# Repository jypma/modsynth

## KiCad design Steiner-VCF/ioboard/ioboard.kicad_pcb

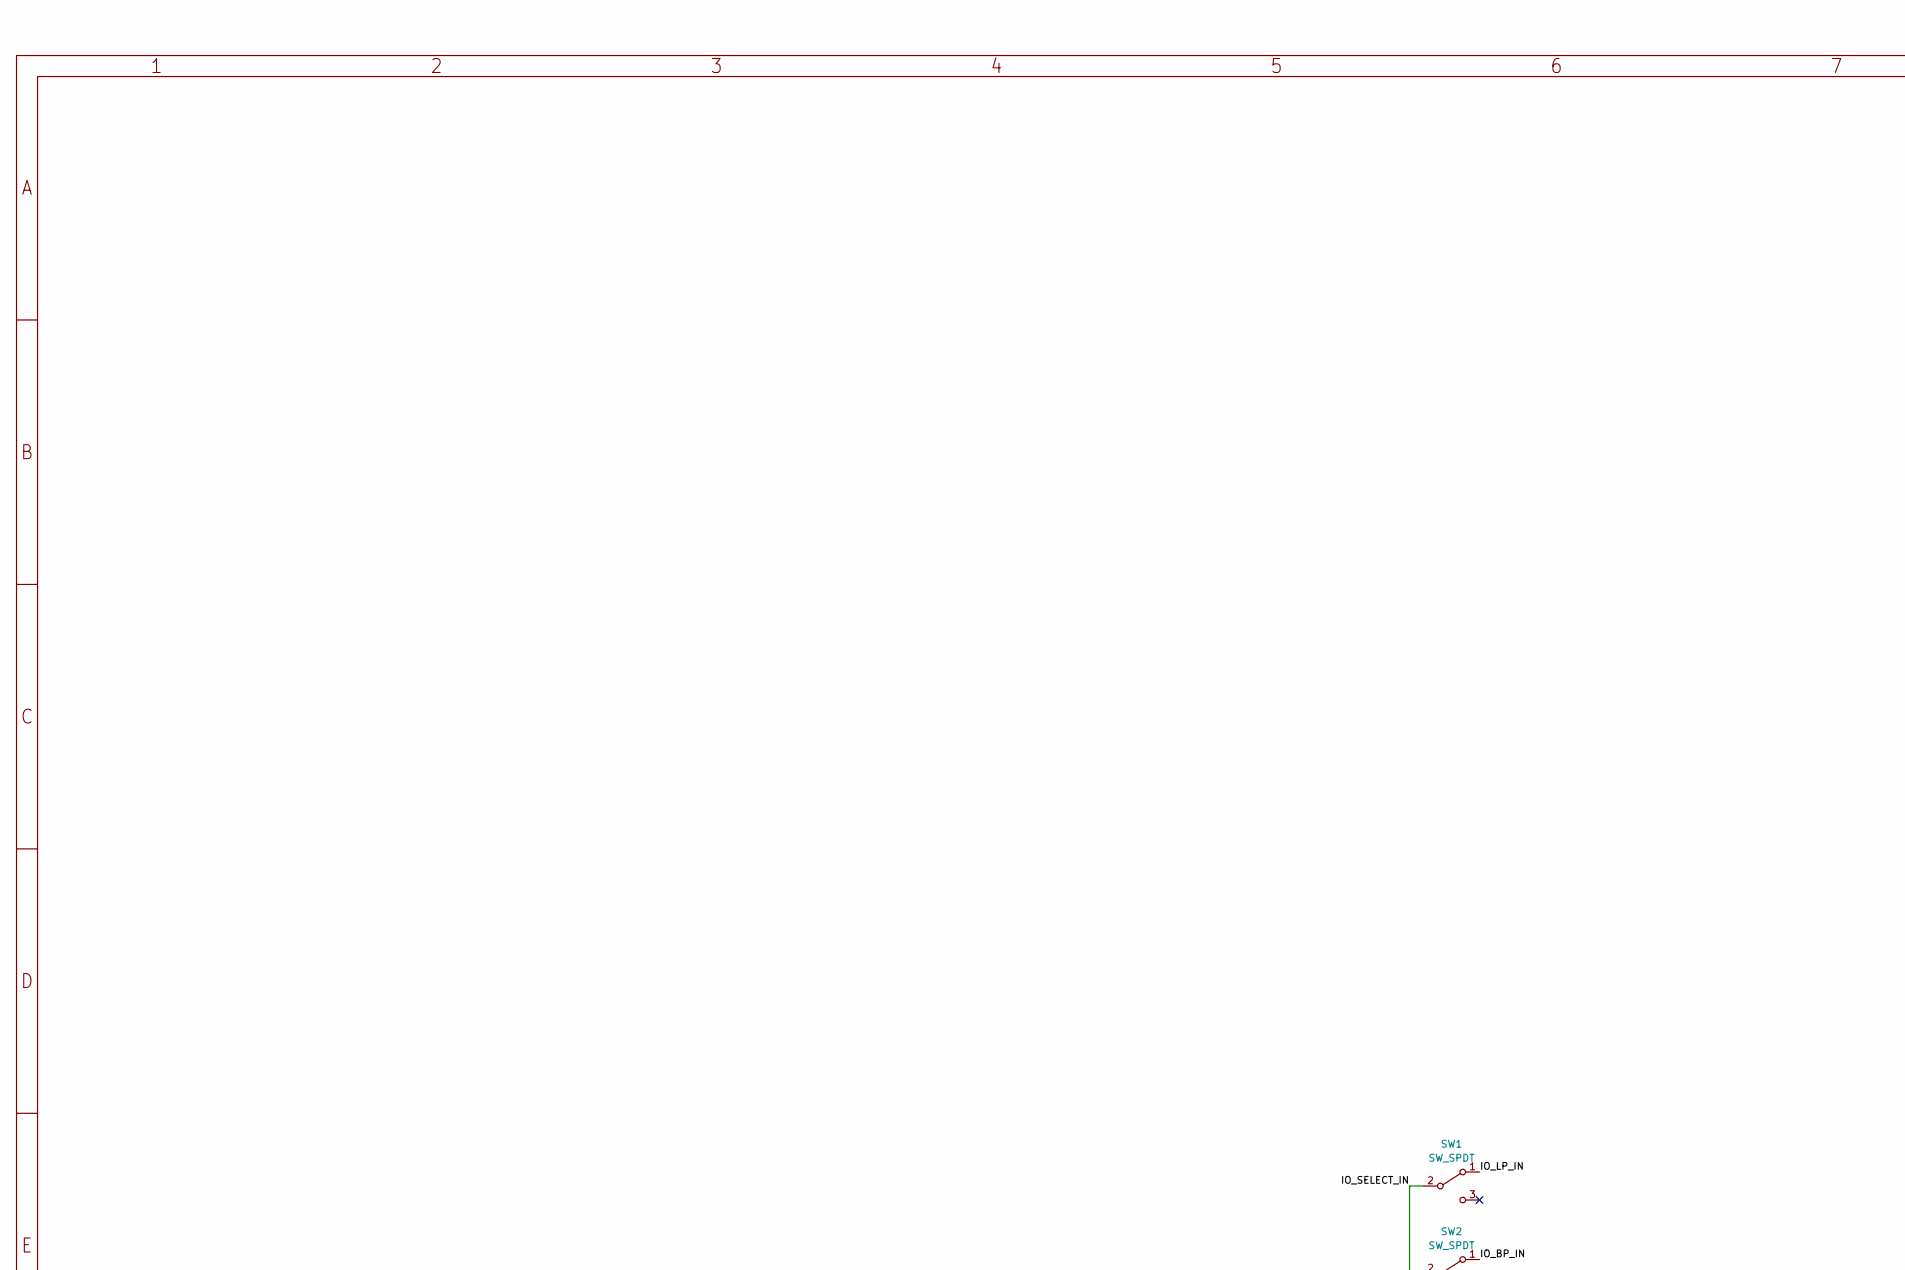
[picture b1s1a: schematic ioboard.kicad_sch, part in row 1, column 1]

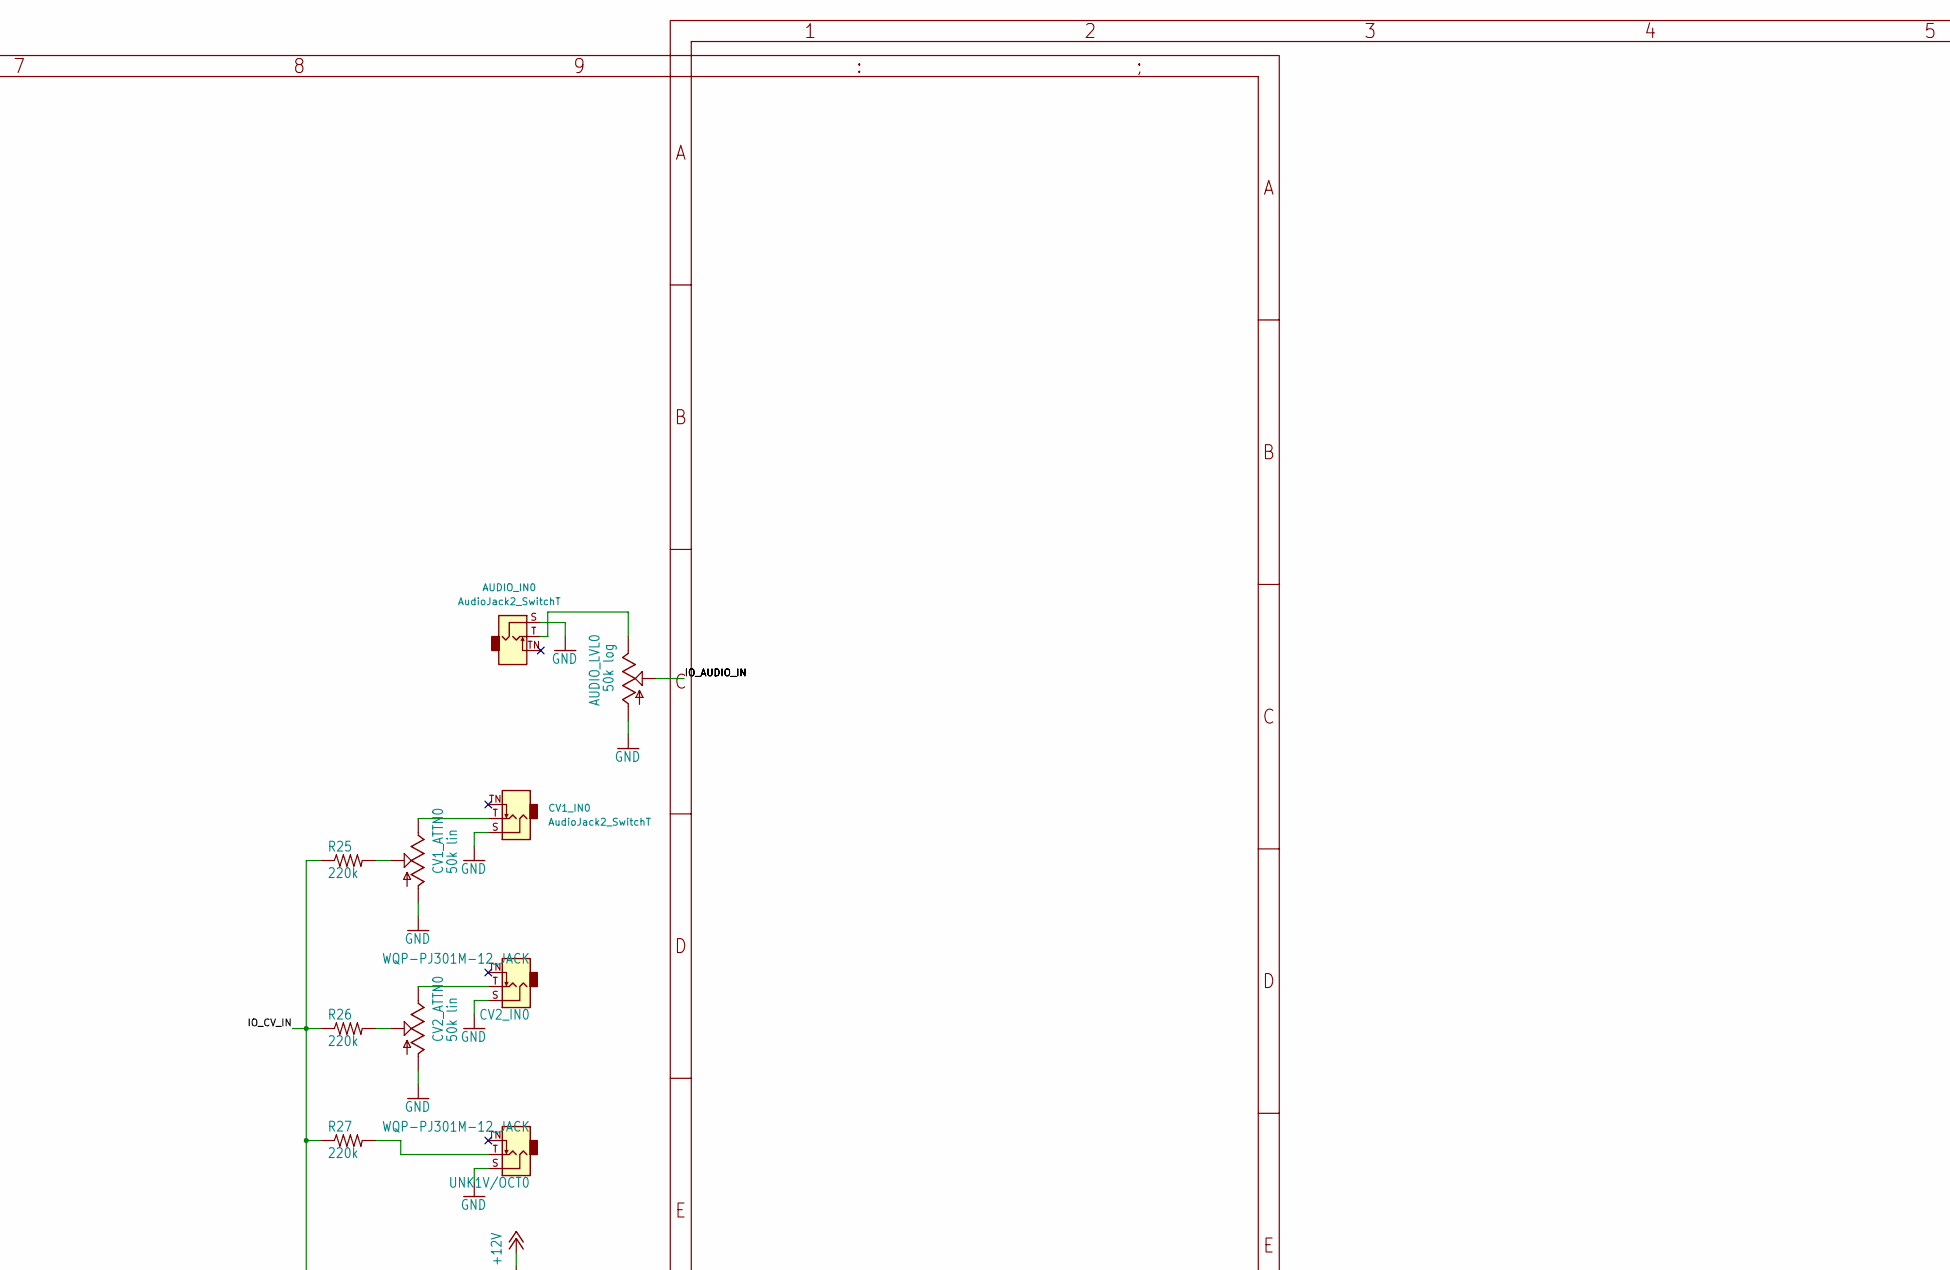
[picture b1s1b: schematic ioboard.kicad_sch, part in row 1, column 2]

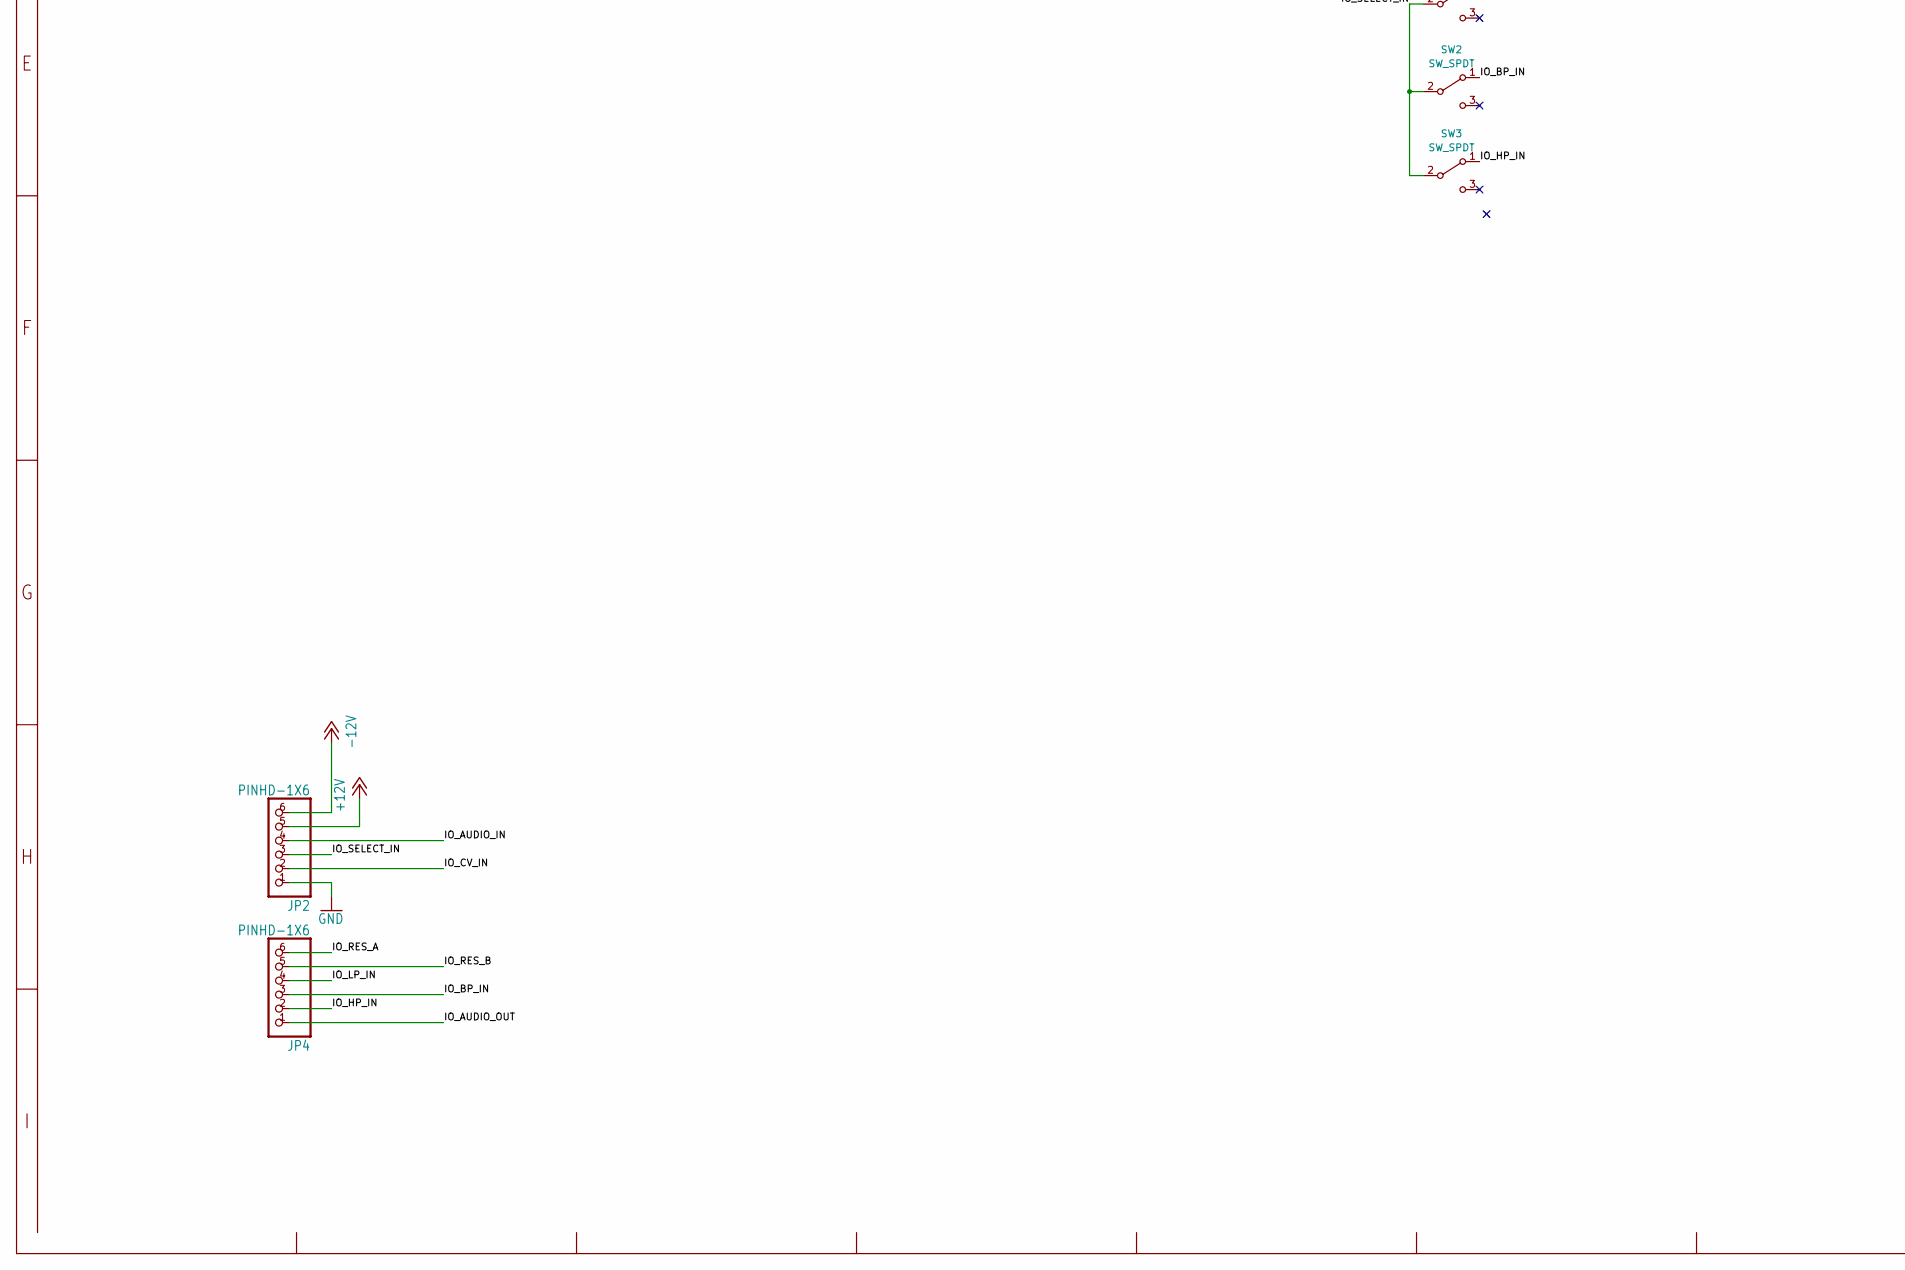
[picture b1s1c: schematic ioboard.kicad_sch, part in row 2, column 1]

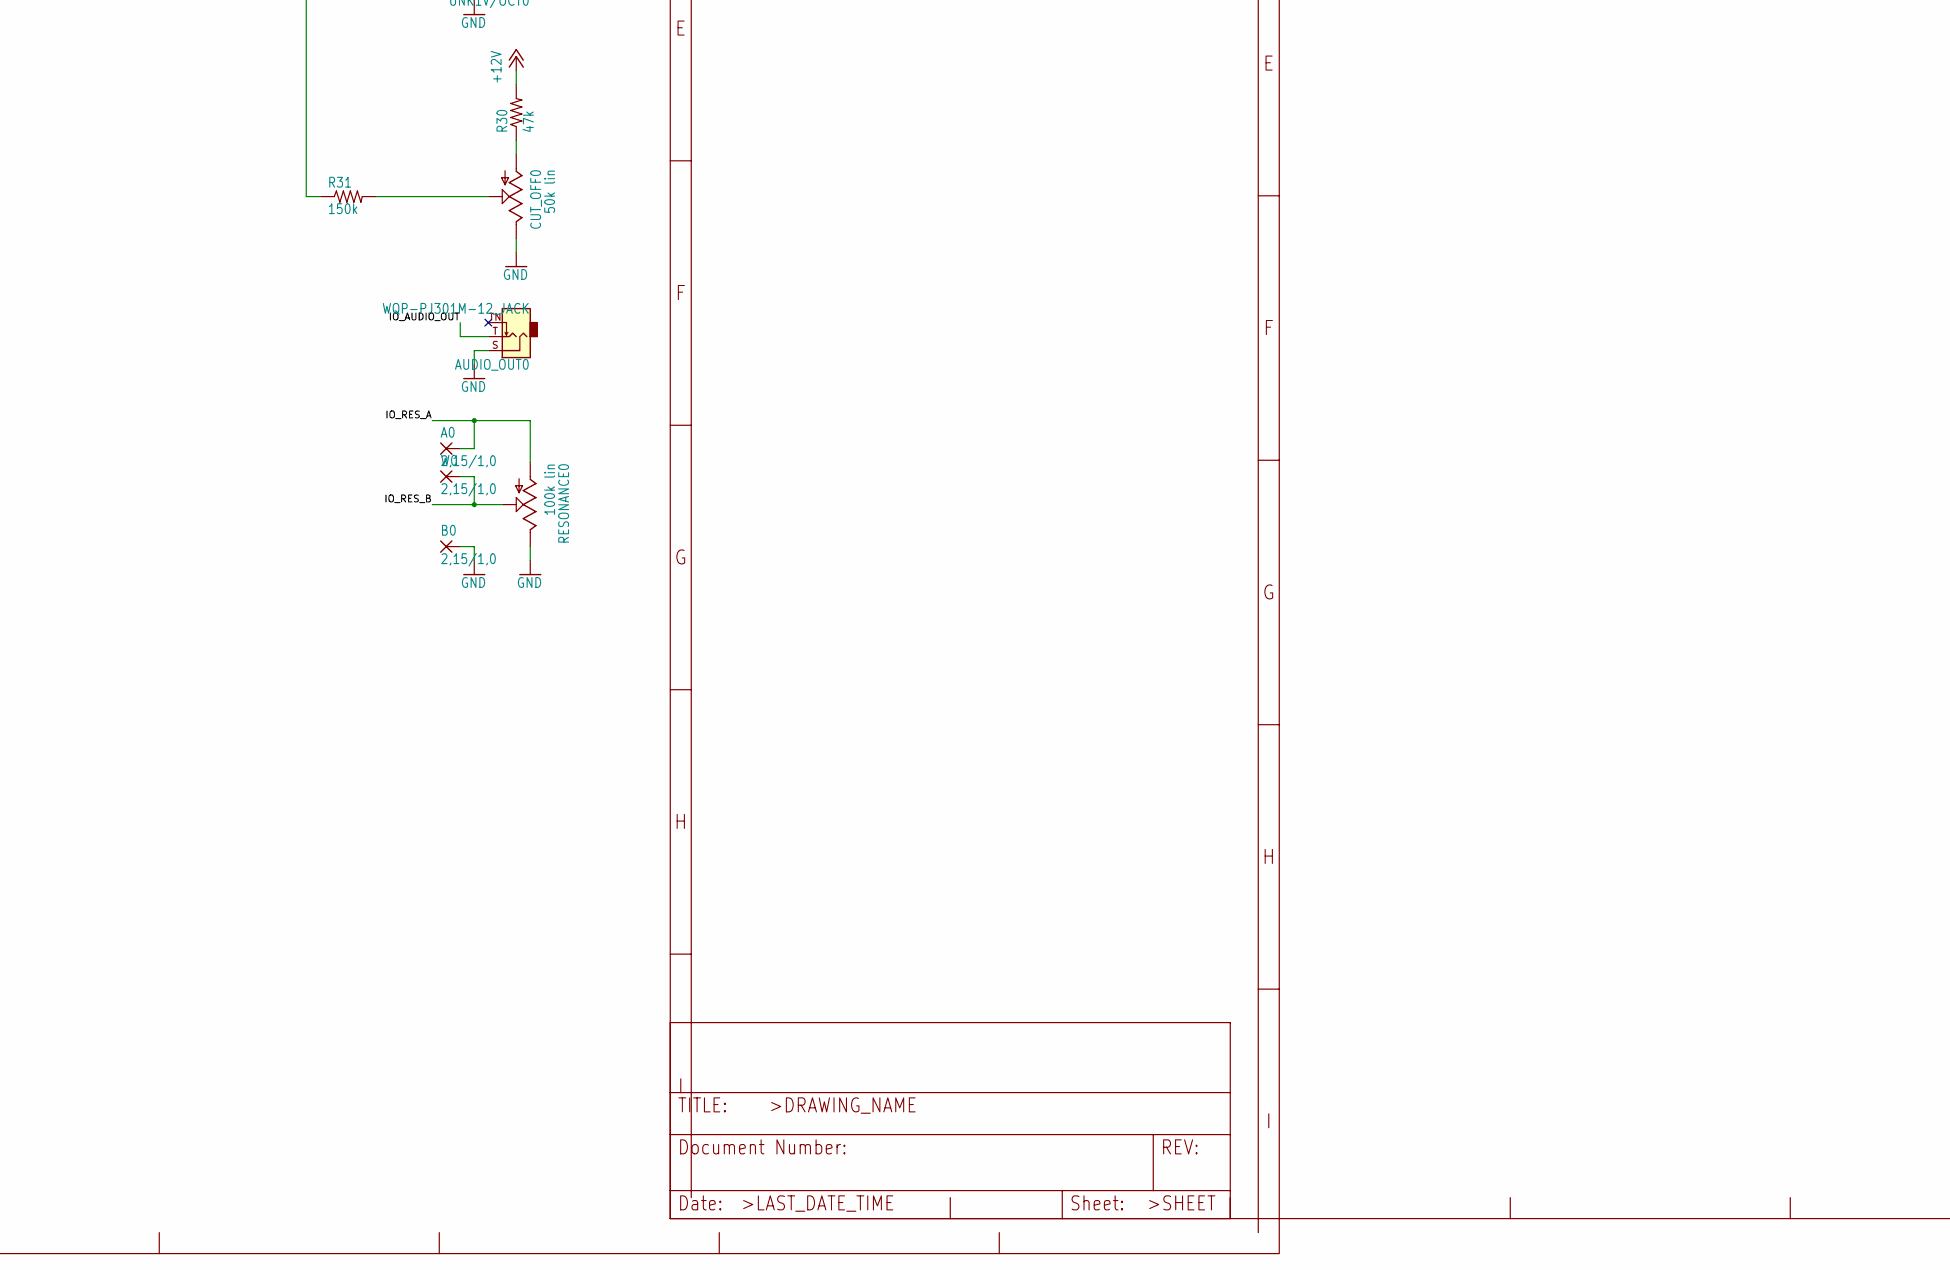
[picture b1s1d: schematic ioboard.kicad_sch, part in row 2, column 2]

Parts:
A0: 2,15/1,0; 2,15_1,0
AUDIO_IN0: AudioJack2_SwitchT; Jack_3.5mm_QingPu_WQP-PJ398SM_Vertical_CircularHoles
AUDIO_LVL0: 50k log; EVUF
AUDIO_OUT0: WQP-PJ301M-12_JACK; Jack_3.5mm_QingPu_WQP-PJ398SM_Vertical_CircularHoles
B0: 2,15/1,0; 2,15_1,0
CUT_OFF0: 50k lin; EVUF
CV1_ATTN0, CV2_ATTN0: 50k lin; EVUF
CV1_IN0: AudioJack2_SwitchT; Jack_3.5mm_QingPu_WQP-PJ398SM_Vertical_CircularHoles
CV2_IN0: WQP-PJ301M-12_JACK; Jack_3.5mm_QingPu_WQP-PJ398SM_Vertical_CircularHoles
JP2, JP4: PINHD-1X6; 1X06
R25, R26, R27: 220k; 0204_7
R30: 47k; 0204_7
R31: 150k; 0204_7
RESONANCE0: 100k lin; EVUF
SW1, SW2, SW3: SW_SPDT; SW_Toggle_Blue_wSlots
UNK1V/OCT0: WQP-PJ301M-12_JACK; Jack_3.5mm_QingPu_WQP-PJ398SM_Vertical_CircularHoles
W0: 2,15/1,0; 2,15_1,0

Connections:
+12V: JP2.5, R30.2
-12V: JP2.6
/IO_AUDIO_IN: AUDIO_LVL0.2 (S), JP2.4
/IO_AUDIO_OUT: AUDIO_OUT0.T, JP4.1
/IO_BP_IN: JP4.3, SW2.1 (A)
/IO_CV_IN: JP2.2, R25.1, R26.1, R27.1, R31.1
/IO_HP_IN: JP4.2, SW3.1 (A)
/IO_LP_IN: JP4.4, SW1.1 (A)
/IO_RES_A: A0.1, JP4.6, RESONANCE0.1 (A)
/IO_RES_B: JP4.5, RESONANCE0.2 (S), W0.1
/IO_SELECT_IN: JP2.3, SW1.2 (B), SW2.2 (B), SW3.2 (B)
GND: AUDIO_IN0.S, AUDIO_LVL0.1 (A), AUDIO_OUT0.S, B0.1, CUT_OFF0.3 (E), CV1_ATTN0.1 (A), CV1_IN0.S, CV2_ATTN0.1 (A), CV2_IN0.S, JP2.1, RESONANCE0.3 (E), UNK1V/OCT0.S
unnamed: AUDIO_IN0.T, AUDIO_LVL0.3 (E)
unnamed: CUT_OFF0.1 (A), R30.1
unnamed: CUT_OFF0.2 (S), R31.2
unnamed: CV1_ATTN0.2 (S), R25.2
unnamed: CV1_ATTN0.3 (E), CV1_IN0.T
unnamed: CV2_ATTN0.2 (S), R26.2
unnamed: CV2_ATTN0.3 (E), CV2_IN0.T
unnamed: R27.2, UNK1V/OCT0.T

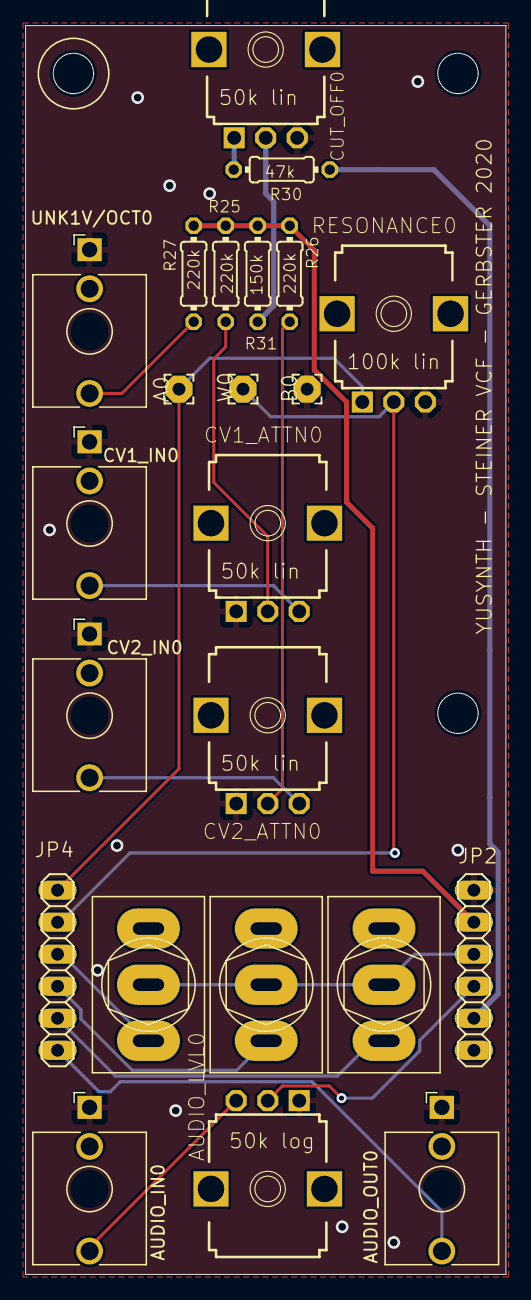
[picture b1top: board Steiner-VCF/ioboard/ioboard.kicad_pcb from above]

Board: 2 copper layers, 38.1 x 99.1 mm, 23 parts (0 on the bottom side), 19 nets.

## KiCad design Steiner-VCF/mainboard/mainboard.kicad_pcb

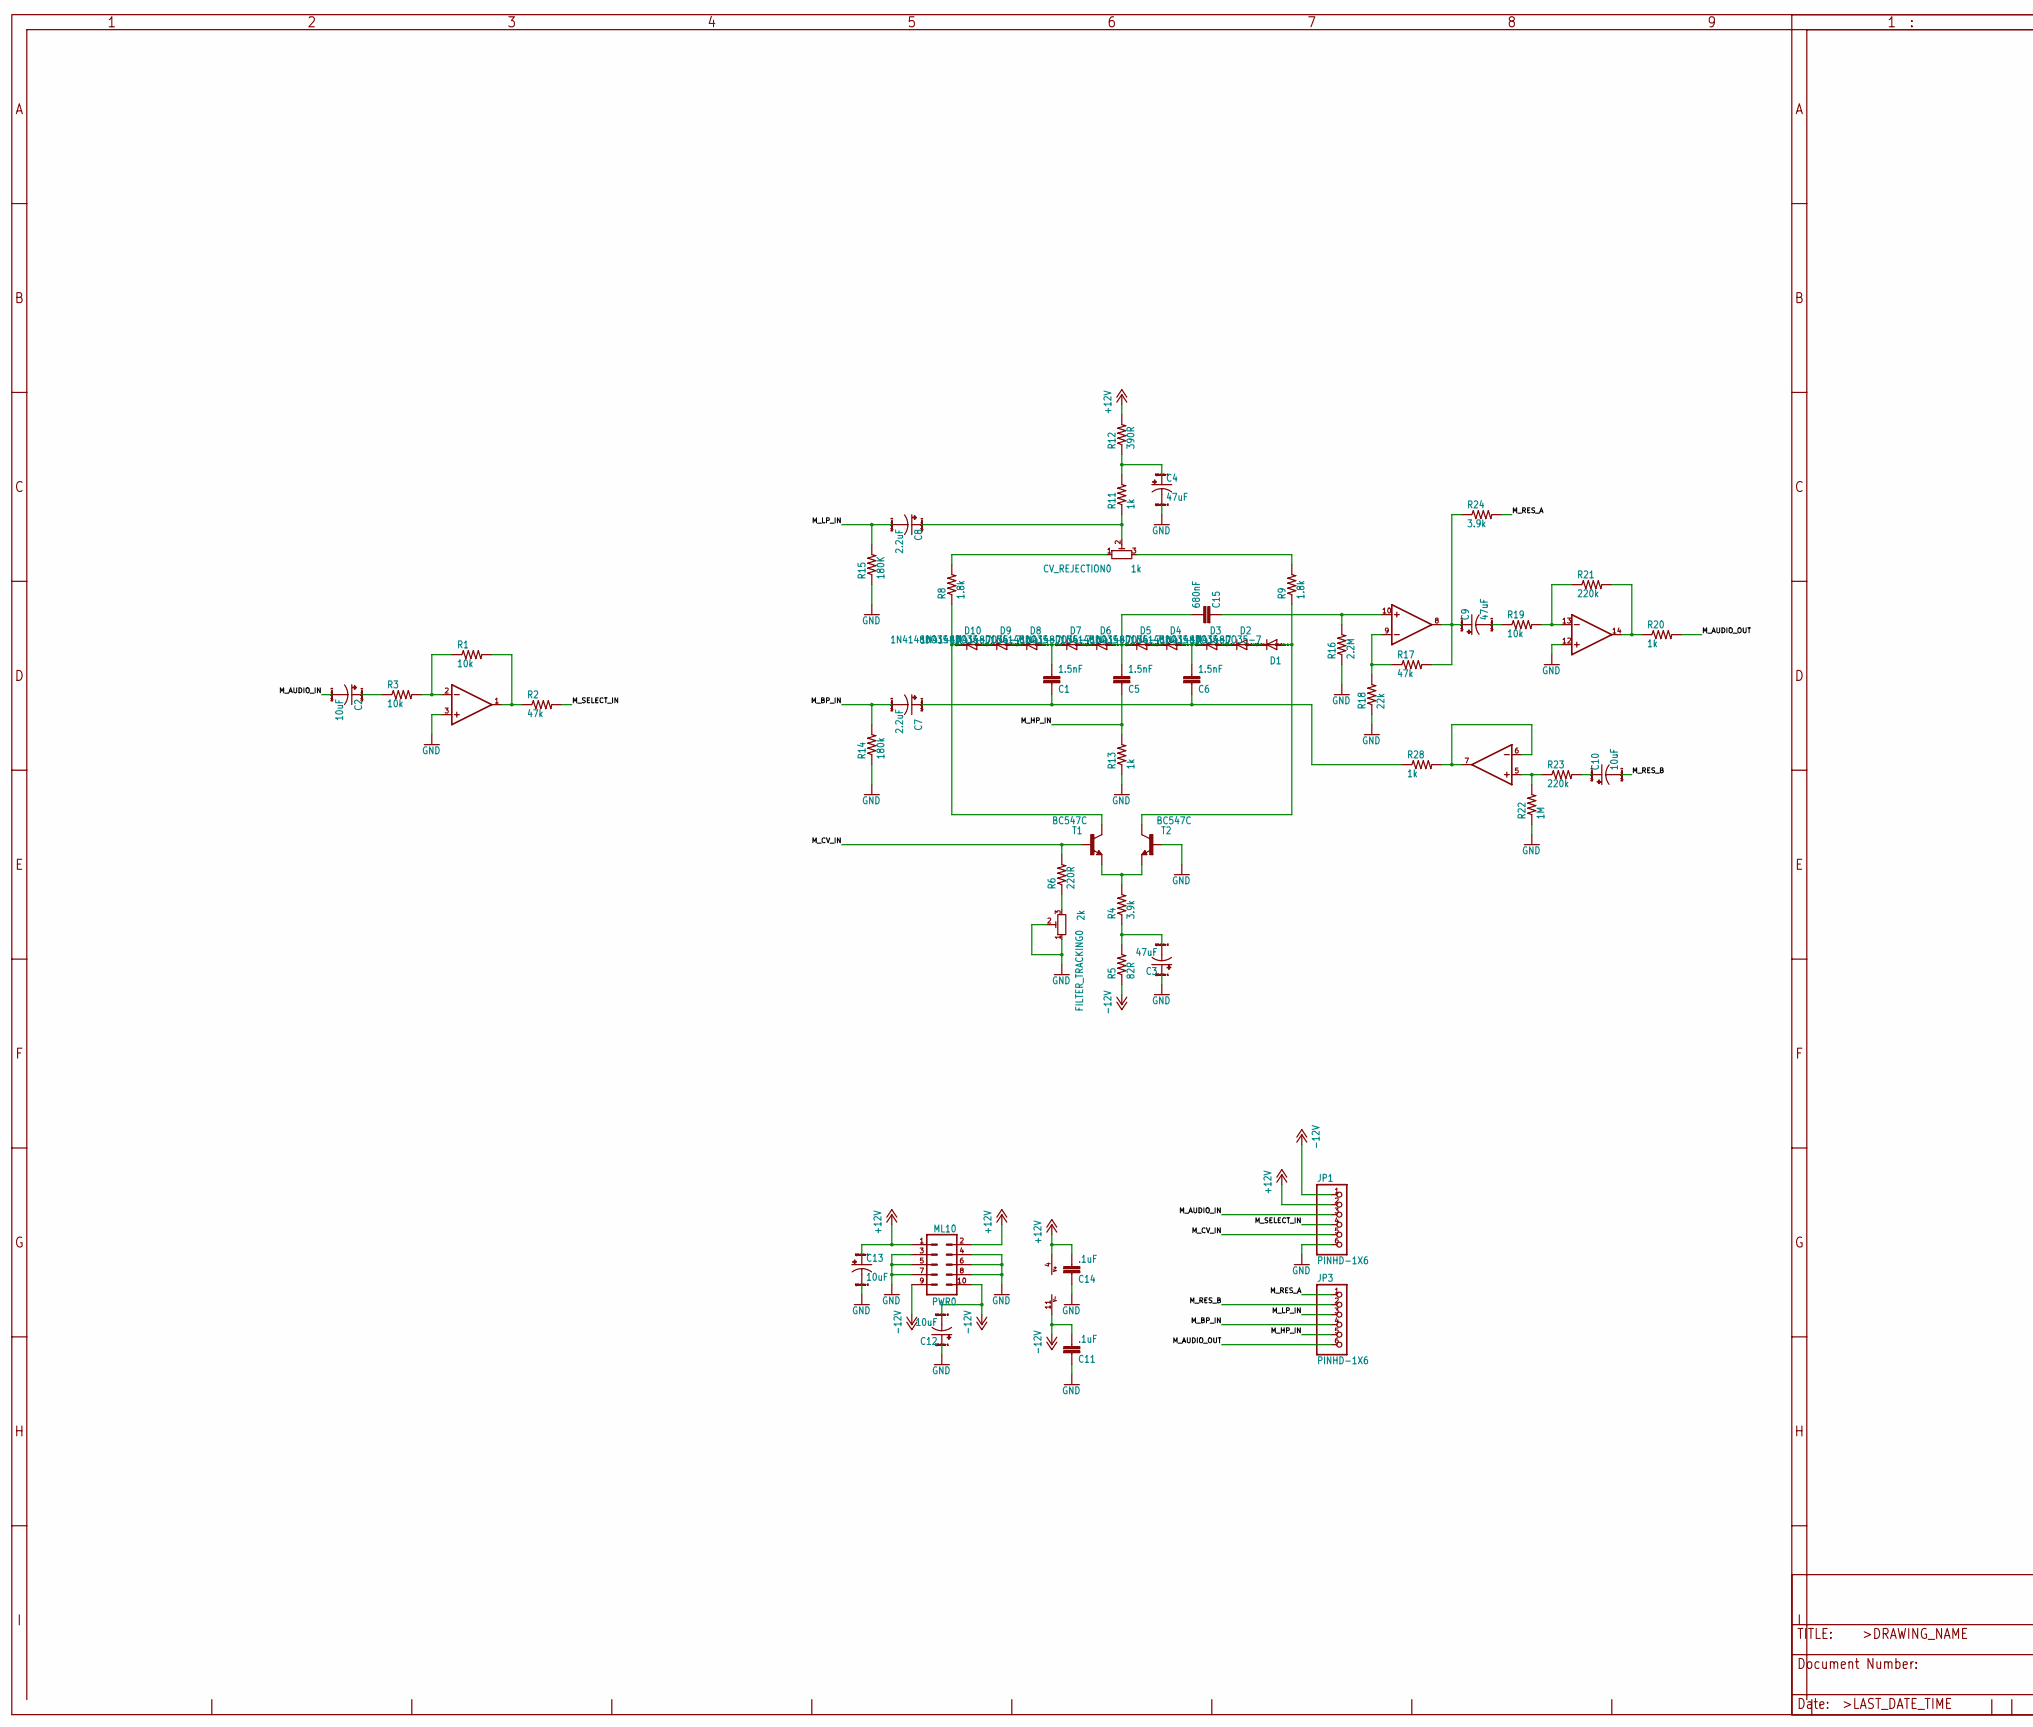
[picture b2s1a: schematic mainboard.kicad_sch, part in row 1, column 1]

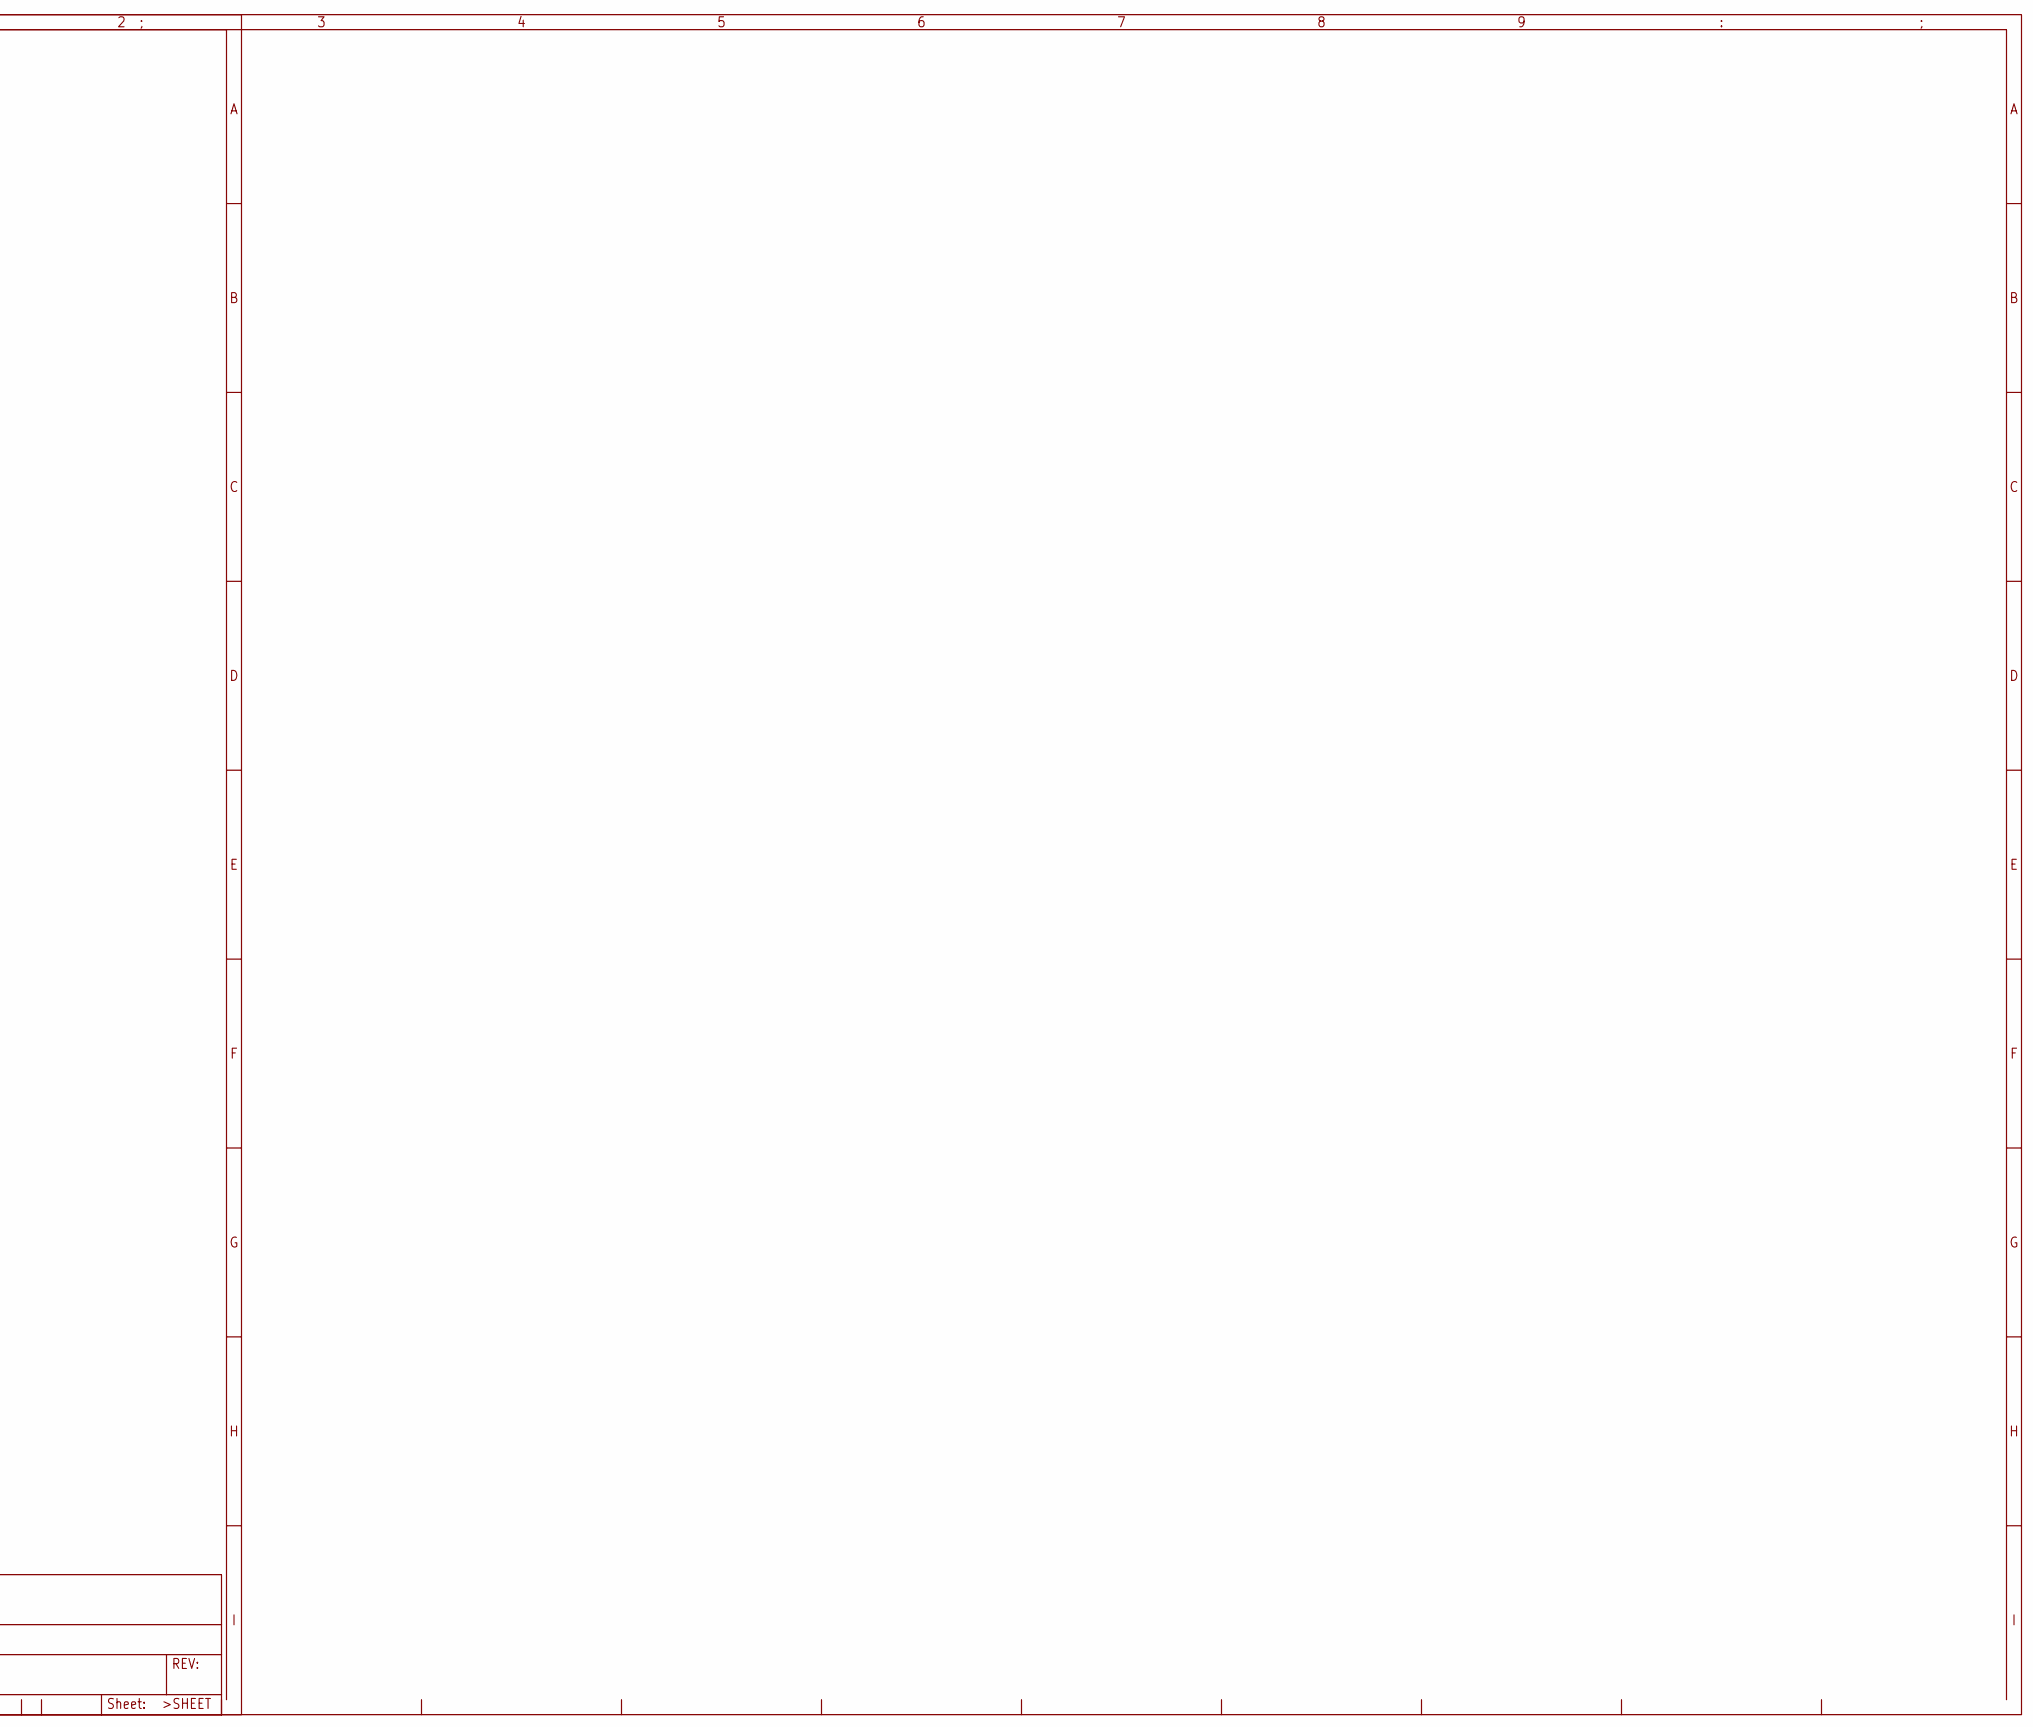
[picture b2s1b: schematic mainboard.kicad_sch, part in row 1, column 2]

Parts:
C1, C5, C6: 1.5nF; C050-024X044
C2, C10, C12, C13: 10uF; E2,5-5
C3, C4, C9: 47uF; E2,5-5
C7, C8: 2.2uF; E2,5-5
C11, C14: .1uF; C050-024X044
C15: 680nF; C050-035X075
CV_REJECTION0: 1k; Potentiometer_Bourns_3296W_Vertical
D1, D2, D3, D4, D5, D6, D7, D8, D9, D10: 1N4148DO35-7; DO35-7
FILTER_TRACKING0: 2k; Potentiometer_Bourns_3296W_Vertical
IC1: TL074P; SOIC-14_3.9x8.7mm_P1.27mm
JP1, JP3: PINHD-1X6; 1X06
PWR0: ML10
R1, R3, R19: 10k; 0204_7
R2, R17: 47k; 0204_7
R4, R24: 3.9k; 0204_7
R5: 82R; 0204_7
R6: 220R; 0204_7
R8, R9: 1.8k; 0204_7
R11, R13, R20, R28: 1k; 0204_7
R12: 390R; 0204_7
R14: 180k; 0204_7
R15: 180K; 0204_7
R16: 2.2M; 0204_7
R18: 22k; 0204_7
R21, R23: 220k; 0204_7
R22: 1M; 0204_7
T1, T2: BC547C; TO92-CBE

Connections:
+12V: C13.+, C14.1, IC1.4 (V+), JP1.2, PWR0.1, PWR0.2, R12.2
-12V: C11.1, C12.-, IC1.11 (V-), JP1.1, PWR0.9, PWR0.10, R5.1
/M_AUDIO_IN: C2.-, JP1.3
/M_AUDIO_OUT: JP3.6, R20.2
/M_BP_IN: C7.-, JP3.4, R14.2
/M_CV_IN: JP1.5, R6.2, T1.B
/M_HP_IN: C5.2, JP3.5, R13.2
/M_LP_IN: C8.-, JP3.3, R15.2
/M_RES_A: JP3.1, R24.2
/M_RES_B: C10.-, JP3.2
/M_SELECT_IN: JP1.4, R2.2
GND: C3.+, C4.-, C11.2, C12.+, C13.-, C14.2, FILTER_TRACKING0.1, FILTER_TRACKING0.2, IC1.3 (+IN), IC1.12 (+IN), JP1.6, PWR0.3, PWR0.4, PWR0.5, PWR0.6, PWR0.7, PWR0.8, R13.1, R14.1, R15.1, R16.1, R18.1, R22.1, T2.B
unnamed: C1.1, D7.C, D8.A
unnamed: C1.2, C6.2, C7.+, R28.1
unnamed: C2.+, R3.1
unnamed: C3.-, R4.1, R5.2
unnamed: C4.+, R11.2, R12.1
unnamed: C6.1, D3.C, D4.A
unnamed: C8.+, CV_REJECTION0.2, R11.1
unnamed: C9.+, IC1.8 (OUT), R17.2, R24.1
unnamed: C9.-, R19.1
unnamed: C10.+, R23.2
unnamed: C5.1, C15.1, D5.C, D6.A
unnamed: C15.2, IC1.10 (+IN), R16.2
unnamed: CV_REJECTION0.3, R9.2
unnamed: D1.A, R9.1, T2.C
unnamed: D1.C, D2.A
unnamed: D2.C, D3.A
unnamed: D4.C, D5.A
unnamed: D6.C, D7.A
unnamed: D8.C, D9.A
unnamed: D9.C, D10.A
unnamed: D10.C, R8.1, T1.C
unnamed: FILTER_TRACKING0.3, R6.1
unnamed: IC1.1 (OUT), R1.2, R2.1
unnamed: IC1.2 (-IN), R1.1, R3.2
unnamed: IC1.5 (+IN), R22.2, R23.1
unnamed: IC1.6 (-IN), IC1.7 (OUT), R28.2
unnamed: IC1.9 (-IN), R17.1, R18.2
unnamed: IC1.13 (-IN), R19.2, R21.1
unnamed: IC1.14 (OUT), R20.1, R21.2
unnamed: R4.2, T1.E, T2.E
unnamed: CV_REJECTION0.1, R8.2

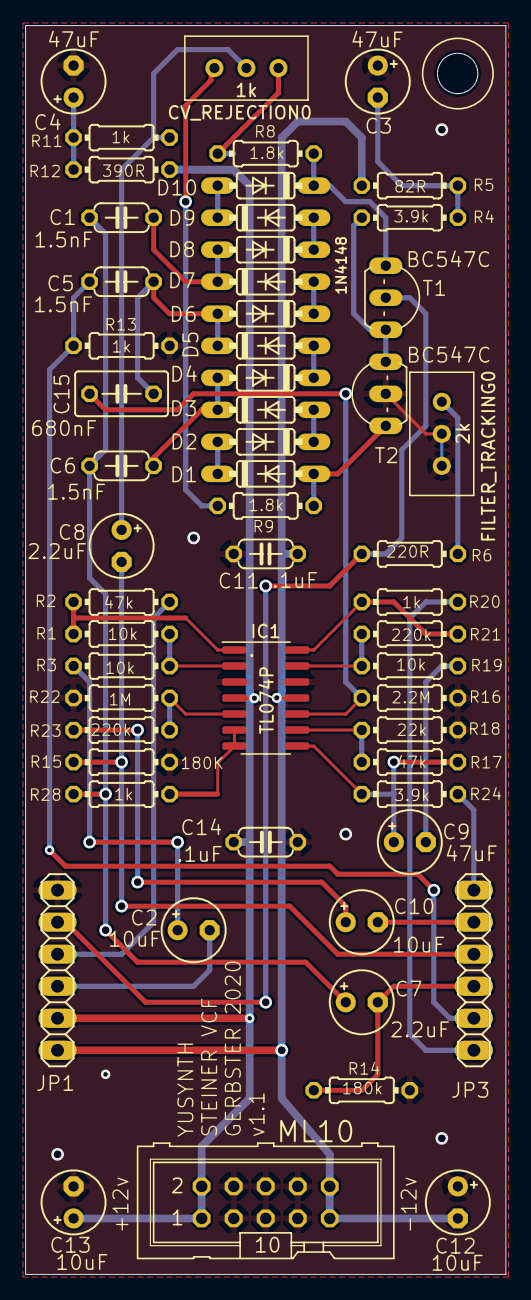
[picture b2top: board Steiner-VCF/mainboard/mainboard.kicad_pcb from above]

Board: 2 copper layers, 38.1 x 99.1 mm, 56 parts (0 on the bottom side), 43 nets.

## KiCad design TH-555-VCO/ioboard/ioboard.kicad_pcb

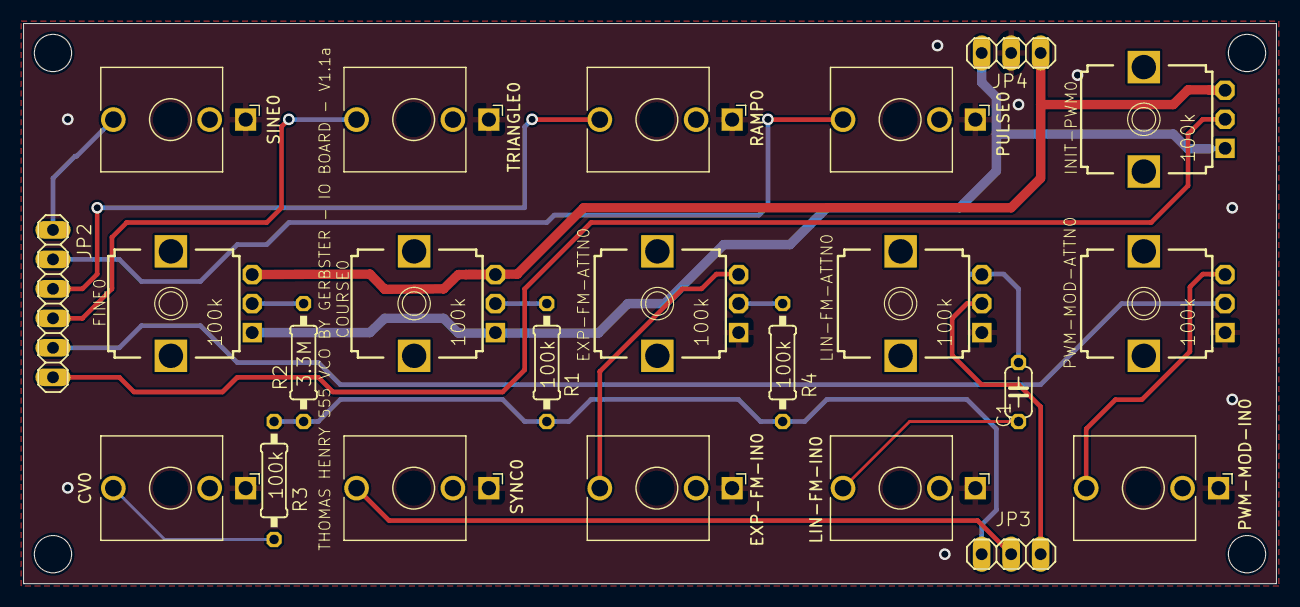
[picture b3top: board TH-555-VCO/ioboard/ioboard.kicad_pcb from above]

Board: 2 copper layers, 108.0 x 48.3 mm, 27 parts (0 on the bottom side), 20 nets.

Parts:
@HOLE0, @HOLE1, @HOLE2, @HOLE3: (no value)
C1: .22uf; C050-024X044
COURSE0: 100k; EVUF
CV0: PJ301BMPJ301BM; Jack_3.5mm_QingPu_WQP-PJ398SM_Eagle
EXP-FM-ATTN0: 100k; EVUF
EXP-FM-IN0: PJ301BMPJ301BM; Jack_3.5mm_QingPu_WQP-PJ398SM_Eagle
FINE0: 100k; EVUF
INIT-PWM0: 100k; EVUF
JP2: 1X06
JP3, JP4: 1X03
LIN-FM-ATTN0: 100k; EVUF
LIN-FM-IN0: PJ301BMPJ301BM; Jack_3.5mm_QingPu_WQP-PJ398SM_Eagle
PULSE0: PJ301BMPJ301BM; Jack_3.5mm_QingPu_WQP-PJ398SM_Eagle
PWM-MOD-ATTN0: 100k; EVUF
PWM-MOD-IN0: PJ301BMPJ301BM; Jack_3.5mm_QingPu_WQP-PJ398SM_Eagle
R1, R3, R4: 100k; 0207_10
R2: 3.3M; 0207_10
RAMP0: PJ301BMPJ301BM; Jack_3.5mm_QingPu_WQP-PJ398SM_Eagle
SINE0: PJ301BMPJ301BM; Jack_3.5mm_QingPu_WQP-PJ398SM_Eagle
SYNC0: PJ301BMPJ301BM; Jack_3.5mm_QingPu_WQP-PJ398SM_Eagle
TRIANGLE0: PJ301BMPJ301BM; Jack_3.5mm_QingPu_WQP-PJ398SM_Eagle

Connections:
1V/OCT: CV0.TIP, R3.1
+12V: COURSE0.3, FINE0.3, INIT-PWM0.3, JP4.1
-12V: COURSE0.1, FINE0.1, INIT-PWM0.1, JP4.3
COARSE: COURSE0.2, R1.1
EXP-FM: EXP-FM-ATTN0.3, EXP-FM-IN0.TIP
EXP-FM-ATTN: EXP-FM-ATTN0.2, R4.1
FINE: FINE0.2, R2.1
GND: CV0.GND1, EXP-FM-ATTN0.1, EXP-FM-IN0.GND1, JP4.2, LIN-FM-ATTN0.1, LIN-FM-IN0.GND1, PULSE0.GND1, PWM-MOD-ATTN0.1, PWM-MOD-IN0.GND1, RAMP0.GND1, SINE0.GND1, SYNC0.GND1, TRIANGLE0.GND1
HARD-SYNC: JP3.2, SYNC0.TIP
LIN-FM: JP3.3, LIN-FM-ATTN0.2
MULTI-IN: JP3.1, R1.2, R2.2, R3.2, R4.2
unnamed: PWM-MOD-ATTN0.3, PWM-MOD-IN0.TIP
unnamed: C1.2, LIN-FM-ATTN0.3
unnamed: C1.1, LIN-FM-IN0.TIP
PULSE-OUT: JP2.2, PULSE0.TIP
PULSE-WIDTH: INIT-PWM0.2, JP2.6
PWM-IN: JP2.5, PWM-MOD-ATTN0.2
RAMP-OUT: JP2.3, RAMP0.TIP
SINE-OUT: JP2.1, SINE0.TIP
TRI-OUT: JP2.4, TRIANGLE0.TIP

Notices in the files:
TuringMachine/TuringBack/TuringBack.kicad_pcb:
March 2016 CC-BY-SA
